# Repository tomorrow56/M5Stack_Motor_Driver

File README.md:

# M5Stack_Motor_Driver

## Motor Driver: L293D (Texas Instruments)
- datasheet: http://www.ti.com/lit/ds/symlink/l293.pdf

## Support page
https://thousandiy.wordpress.com/2018/10/20/motor-driver-shield-for-m5stack/

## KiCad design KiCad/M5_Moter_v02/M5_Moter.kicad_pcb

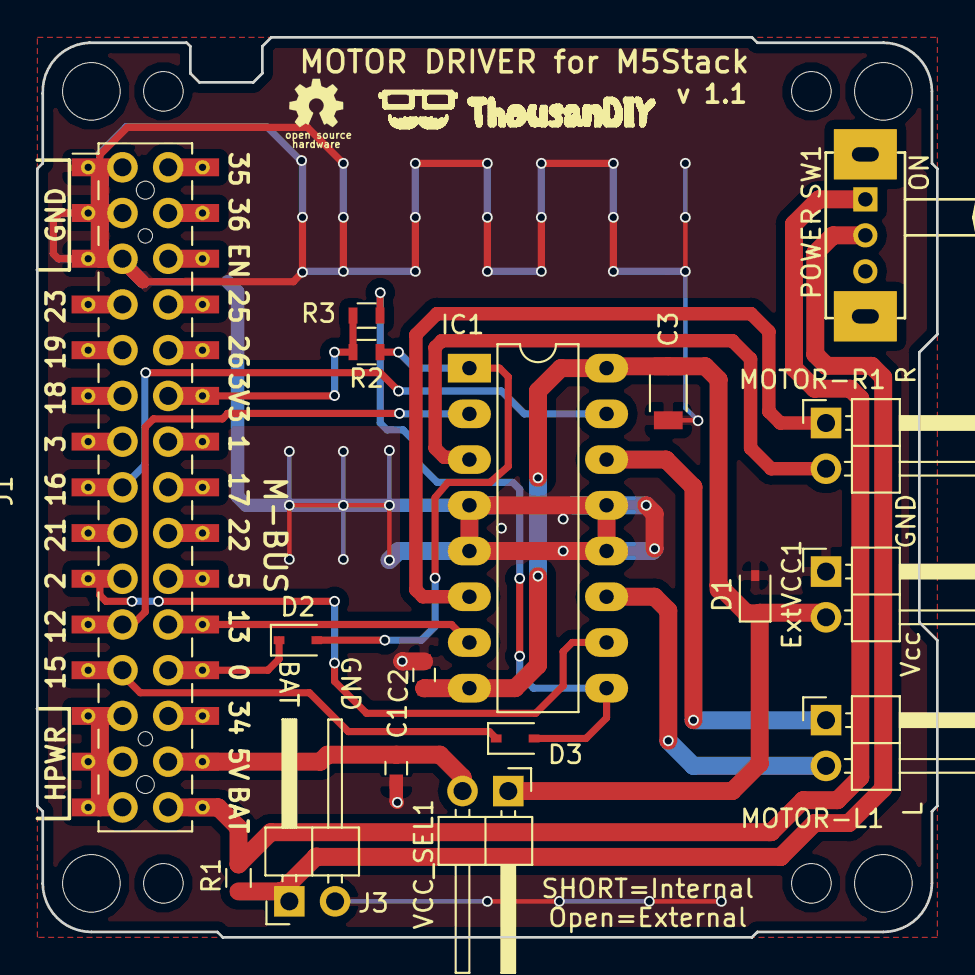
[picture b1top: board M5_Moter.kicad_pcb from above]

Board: 2 copper layers, 50.0 x 50.0 mm, 27 parts (0 on the bottom side), 19 nets.

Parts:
C1, C2: 10uF; C_0603
C3: 100uF; C_1206
D1, D2, D3: 1N4148; D_SOD-323
ExtVCC1: Terminal_01X02_FEMALE; Pin_Header_Angled_1x02_Pitch2.54mm
IC1: L293D; DIP-16_W7.62mm_LongPads
J1: M-BUS; Pin_Header_MBUS_SMD_TH
J3: Battery; Pin_Header_Angled_1x02_Pitch2.54mm
LOGO1: OPEN_HARDWARE_1; OSHW-logo_silkscreen-front_3mm
LOGO_TDIY1: TDIY_LOGO; TDIY-LOGO-S
MK1, MK2, MK3, MK4: Mounting_Hole; MountingHole_3.2mm_M3
MK5, MK6, MK7, MK8: Mounting_Hole; MountingHole_2.2mm_M2
MOTOR-L1: Terminal_01X02_FEMALE; Pin_Header_Angled_1x02_Pitch2.54mm
MOTOR-R1: Terminal_01X02_FEMALE; Pin_Header_Angled_1x02_Pitch2.54mm
R1: 0; R_0603
R2, R3: 10k; R_0603
SW1: SK-12D01-VG4; slide_switch_angled
VCC_SEL1: Terminal_01X02_FEMALE; Pin_Header_Angled_1x02_Pitch2.54mm

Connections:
/+3.3V: J1.12, R2.2, R3.2
/+5V: C1.1, J1.28, VCC_SEL1.2
/VCC: C2.1, C3.1, D1.1, ExtVCC1.2, IC1.8, IC1.16, VCC_SEL1.1
GND: C1.2, C2.2, C3.2, D1.2, ExtVCC1.1, IC1.4, IC1.5, IC1.12, IC1.13, J1.1, J1.3, J1.5, J3.2
IO0: D2.1, J1.24
IO2: IC1.10, J1.19
IO12: IC1.2, J1.21
IO13: IC1.7, J1.22
IO15: D3.1, J1.23
IO16: IC1.15, J1.15
unnamed: D2.2, IC1.1, R2.1
unnamed: D3.2, IC1.9, R3.1
unnamed: IC1.3, MOTOR-R1.2
unnamed: IC1.6, MOTOR-R1.1
unnamed: IC1.11, MOTOR-L1.2
unnamed: IC1.14, MOTOR-L1.1
unnamed: J1.25, J1.27, J1.29
unnamed: J1.30, R1.1, SW1.1
unnamed: J3.1, R1.2, SW1.2

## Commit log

2019-02-07 Add design data
2019-04-29 add case data
2019-05-28 add v03 PCB(GND correction )
2019-05-29 Update KiCad Data
2019-05-29 Add v03
